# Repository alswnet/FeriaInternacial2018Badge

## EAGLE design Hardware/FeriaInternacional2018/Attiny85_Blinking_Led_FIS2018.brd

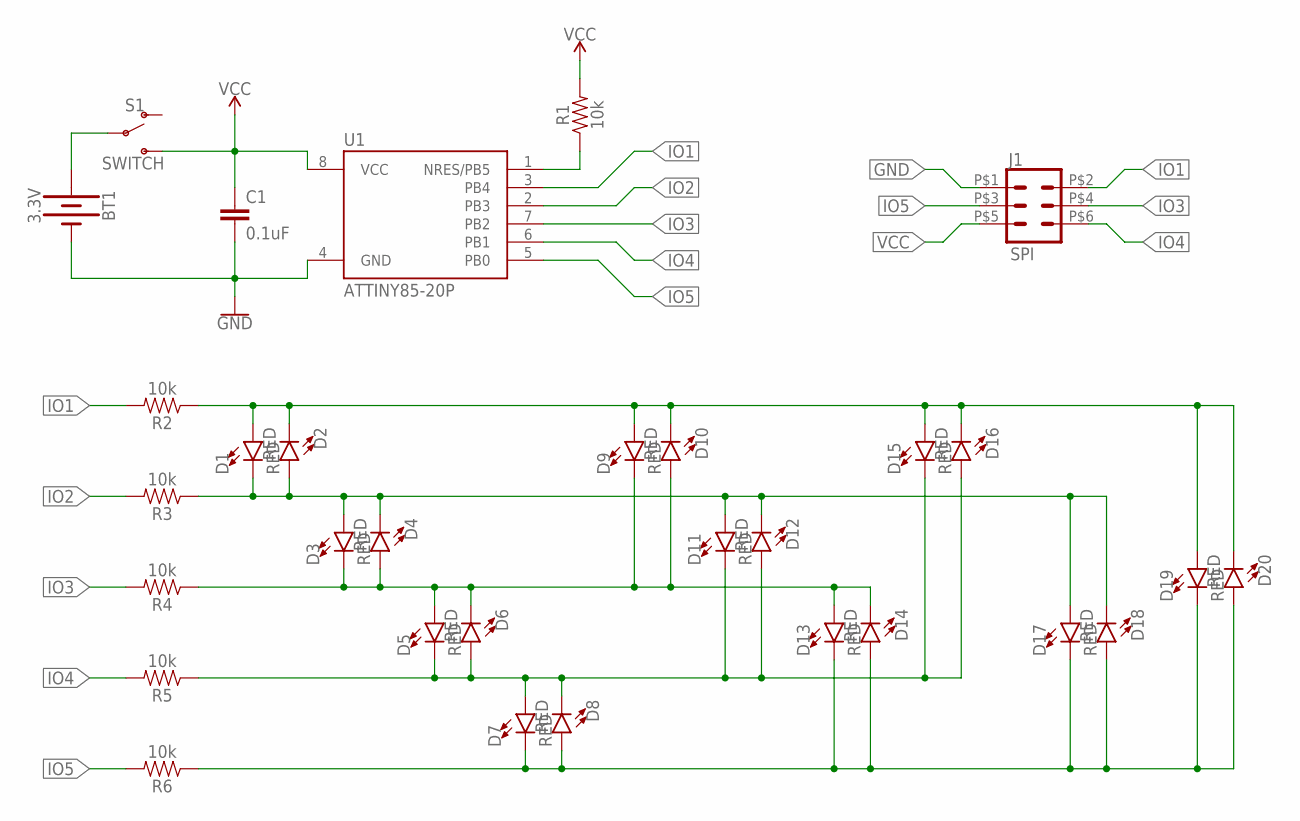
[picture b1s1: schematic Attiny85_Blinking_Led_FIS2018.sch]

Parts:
BT1: 3.3V; BATTCON_20MM_4LEGS
C1: 0.1uF; 0603
D1, D2, D3, D4, D5, D6, D7, D8, D9, D10, D11, D12, D13, D14, D15, D16, D17, D18, D19, D20: RED; LED_3MM
J1: SPI; 2X3_POGO
R1, R2, R3, R4, R5, R6: 10k; AXIAL-0.3
S1: SWITCH; SWITCH_SPST_SMD_A
U1: ATTINY85-20P; PDIP08_300MIL

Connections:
GND: BT1.NEGATIVE (-), C1.2, J1.P$1 (1), U1.4 (GND)
IO1: J1.P$2 (2), R2.P$2 (2), U1.3 (PB4)
IO2: R3.P$2 (2), U1.2 (PB3)
IO3: J1.P$4 (4), R4.P$2 (2), U1.7 (PB2)
IO4: J1.P$6 (6), R5.P$2 (2), U1.6 (PB1)
IO5: J1.P$3 (3), R6.P$2 (2), U1.5 (PB0)
IO11: D1.A, D2.K (C), D9.A, D10.K (C), D15.A, D16.K (C), D19.A, D20.K (C), R2.P$1 (1)
IO22: D1.K (C), D2.A, D3.A, D4.K (C), D11.A, D12.K (C), D17.A, D18.K (C), R3.P$1 (1)
IO33: D3.K (C), D4.A, D5.A, D6.K (C), D9.K (C), D10.A, D13.A, D14.K (C), R4.P$1 (1)
IO44: D5.K (C), D6.A, D7.A, D8.K (C), D11.K (C), D12.A, D15.K (C), D16.A, R5.P$1 (1)
IO55: D7.K (C), D8.A, D13.K (C), D14.A, D17.K (C), D18.A, D19.K (C), D20.A, R6.P$1 (1)
unnamed: R1.P$1 (1), U1.1 (NRES/PB5)
unnamed: BT1.POSITIVE@1 (+), BT1.POSITIVE@2 (+), BT1.POSITIVE@3 (+), BT1.POSITIVE@4 (+), S1.2
VCC: C1.1, J1.P$5 (5), R1.P$2 (2), S1.3 (S), U1.8 (VCC)

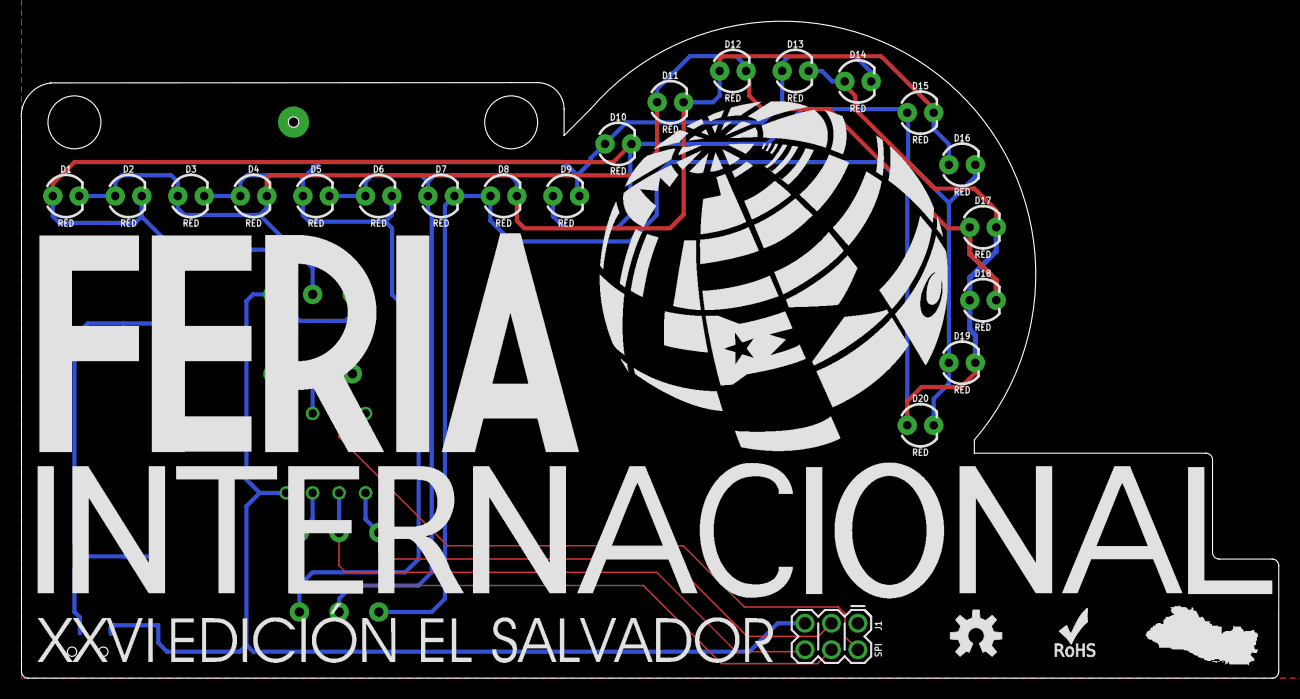
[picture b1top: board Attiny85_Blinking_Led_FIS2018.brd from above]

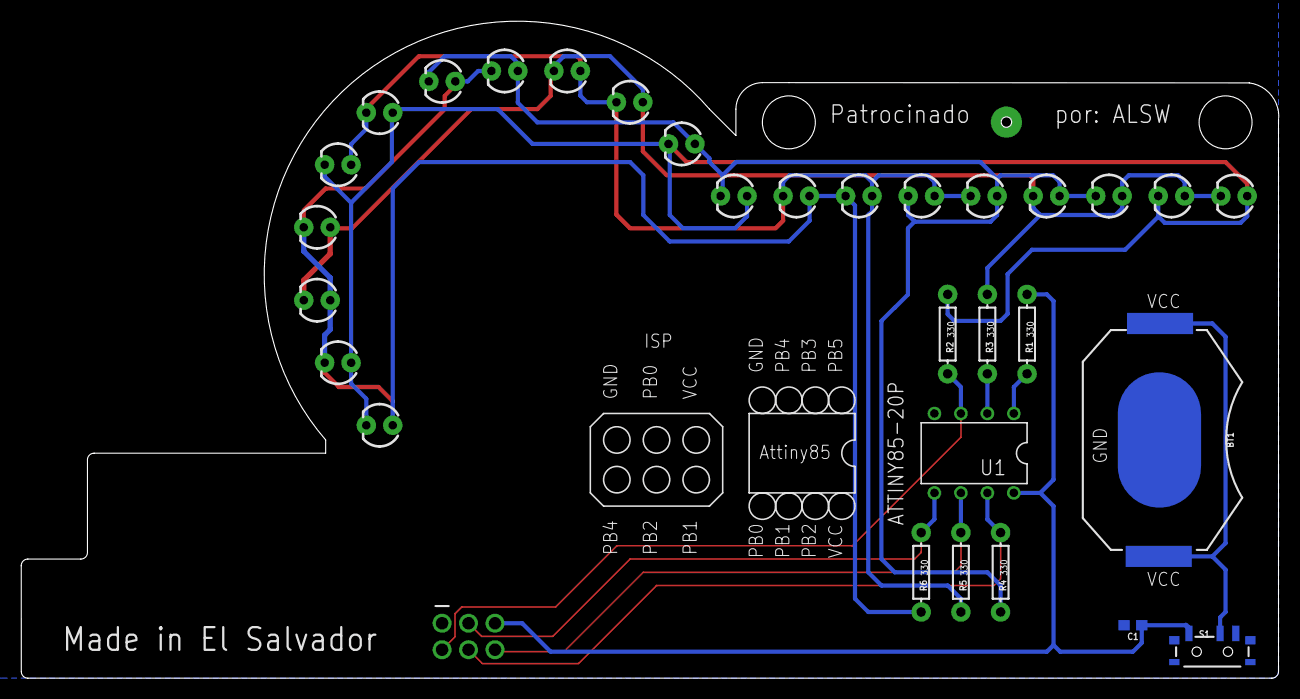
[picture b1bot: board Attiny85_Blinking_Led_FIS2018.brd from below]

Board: 2 copper layers, 120.7 x 63.0 mm, 33 parts (10 on the bottom side), 14 nets.

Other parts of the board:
U$1: OSHW-LOGO-M
U$2: ROHS_LOGO_0.18_IN

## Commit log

2018-10-23 I created a Folder 'Hardware', i did minimal schematic in eagle for a charliplexing with a attiny85, maybe change
2018-10-23 I did a charlieplexing with attiny85, i use 20 leds, i make a board, but inst ready, just i did a file
2018-10-24 Add a SPST switch, order and design a PCB circuit, doenst route yet
2018-10-25 Actualizando imagenes para el diseño
2018-10-30 Disenño de placa, posicion de componentes y ruteo de lineas
2018-10-31 add port spi, has a desing art, add holes for badge and pin
2018-10-31 Generate previews, top face, bottom face, mask face, and final pcb board
2018-10-31 add logo ALSW, reorder route, redimension pcb
2018-10-31 Add el salvador logo, open hardware, add eschamtic attiny and isp
2018-11-07 Order folders

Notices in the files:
parts and their libraries:
SparkFun-Batteries: Licensing: Creative Commons ShareAlike 4.0 International - https://creativecommons.org/licenses/by-sa/4.0
